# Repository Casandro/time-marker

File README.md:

# Time Marker

This is a small device designed to monitor the frequency of power grids.
It consists of a piece of hardware which generates GNSS synced audio markers, and isolates and down-scales it so both can be fed into a sound-card.

From there software will read the markers and generate down-sampled, but propperly timed audio files.

## Overall concept
```
          GNSS (GPS, Galileo, etc)
                   |
Mains grid---Time Marker hardware-----Line-IN of PC

```

## Hardware

The hardware will get an interrupt from the PPS signal from the GNSS receiver as well as the time via serial.
This will start playing a correlation sample, then some data containing the current time.
Optionally you can also put that signal onto an RS-232 port, which is useful for getting the PPS signal into your PC.

## Audio interface
The idea is that soundcards typically have very decent AD converters, usually having sample rates of at least 48kHz and sample depths of at least 16 Bits. It's hard to do that with easy to get chips.
However the clock of those is very much undefined, plus there is an unknown amount of latency between the analog input and the application getting the data.

To circumvent this, the hardware generates markers on one channel, so the other channel is free for whatever signal you want to sample.

### Format

The format is not yet defined, however it'll likely use either FSK or DTMF for the data.
There will be a sync mark at the beginning of the second, since this is when the timing error is lowest. It will be something with good correlation properties.

A DTMF tone typically is recommended to be at least 50 ms long with a pause of 20 ms between two digits. This means that in a second we could have 14 digits. Leaving some room for the second marker and silence at the end, we could, for exmample, have 10 digits per second. One marker, 8 data digits and one parity or stop digit. The advantage is that DTMF has discrete tones so we can easily have a gap at the end of the signal.

With FSK, we could, for example, have V.21 modulated bits. We'd probably have something like 256 data bits when we subtract run-in periods and the like. We probably need to re-sync it as part of the second mark.

## Software
No software is written so far, however it would probably work like this:

1. Determine the exact position of the second markers via cross correlation and sub sample interpolation. (The auto-correlation function will likely be triangular around it's center which we can use for sub sample accuracy)
2. Resample the second in the desired sample rate (e.g. 200 Hz)
3. Demodulate the data part of the signal to determine what second is read.
4. Store / process that second of data

Since we will likely not be able to get good data on harmonics, it may be sensible to only look at the 50 Hz peak. For this we can do an IQ demodulation at 50 Hz, downsample this to, for example, 10 or 25 Hz, and only store that IQ data. In principle we can also just store the phase data.

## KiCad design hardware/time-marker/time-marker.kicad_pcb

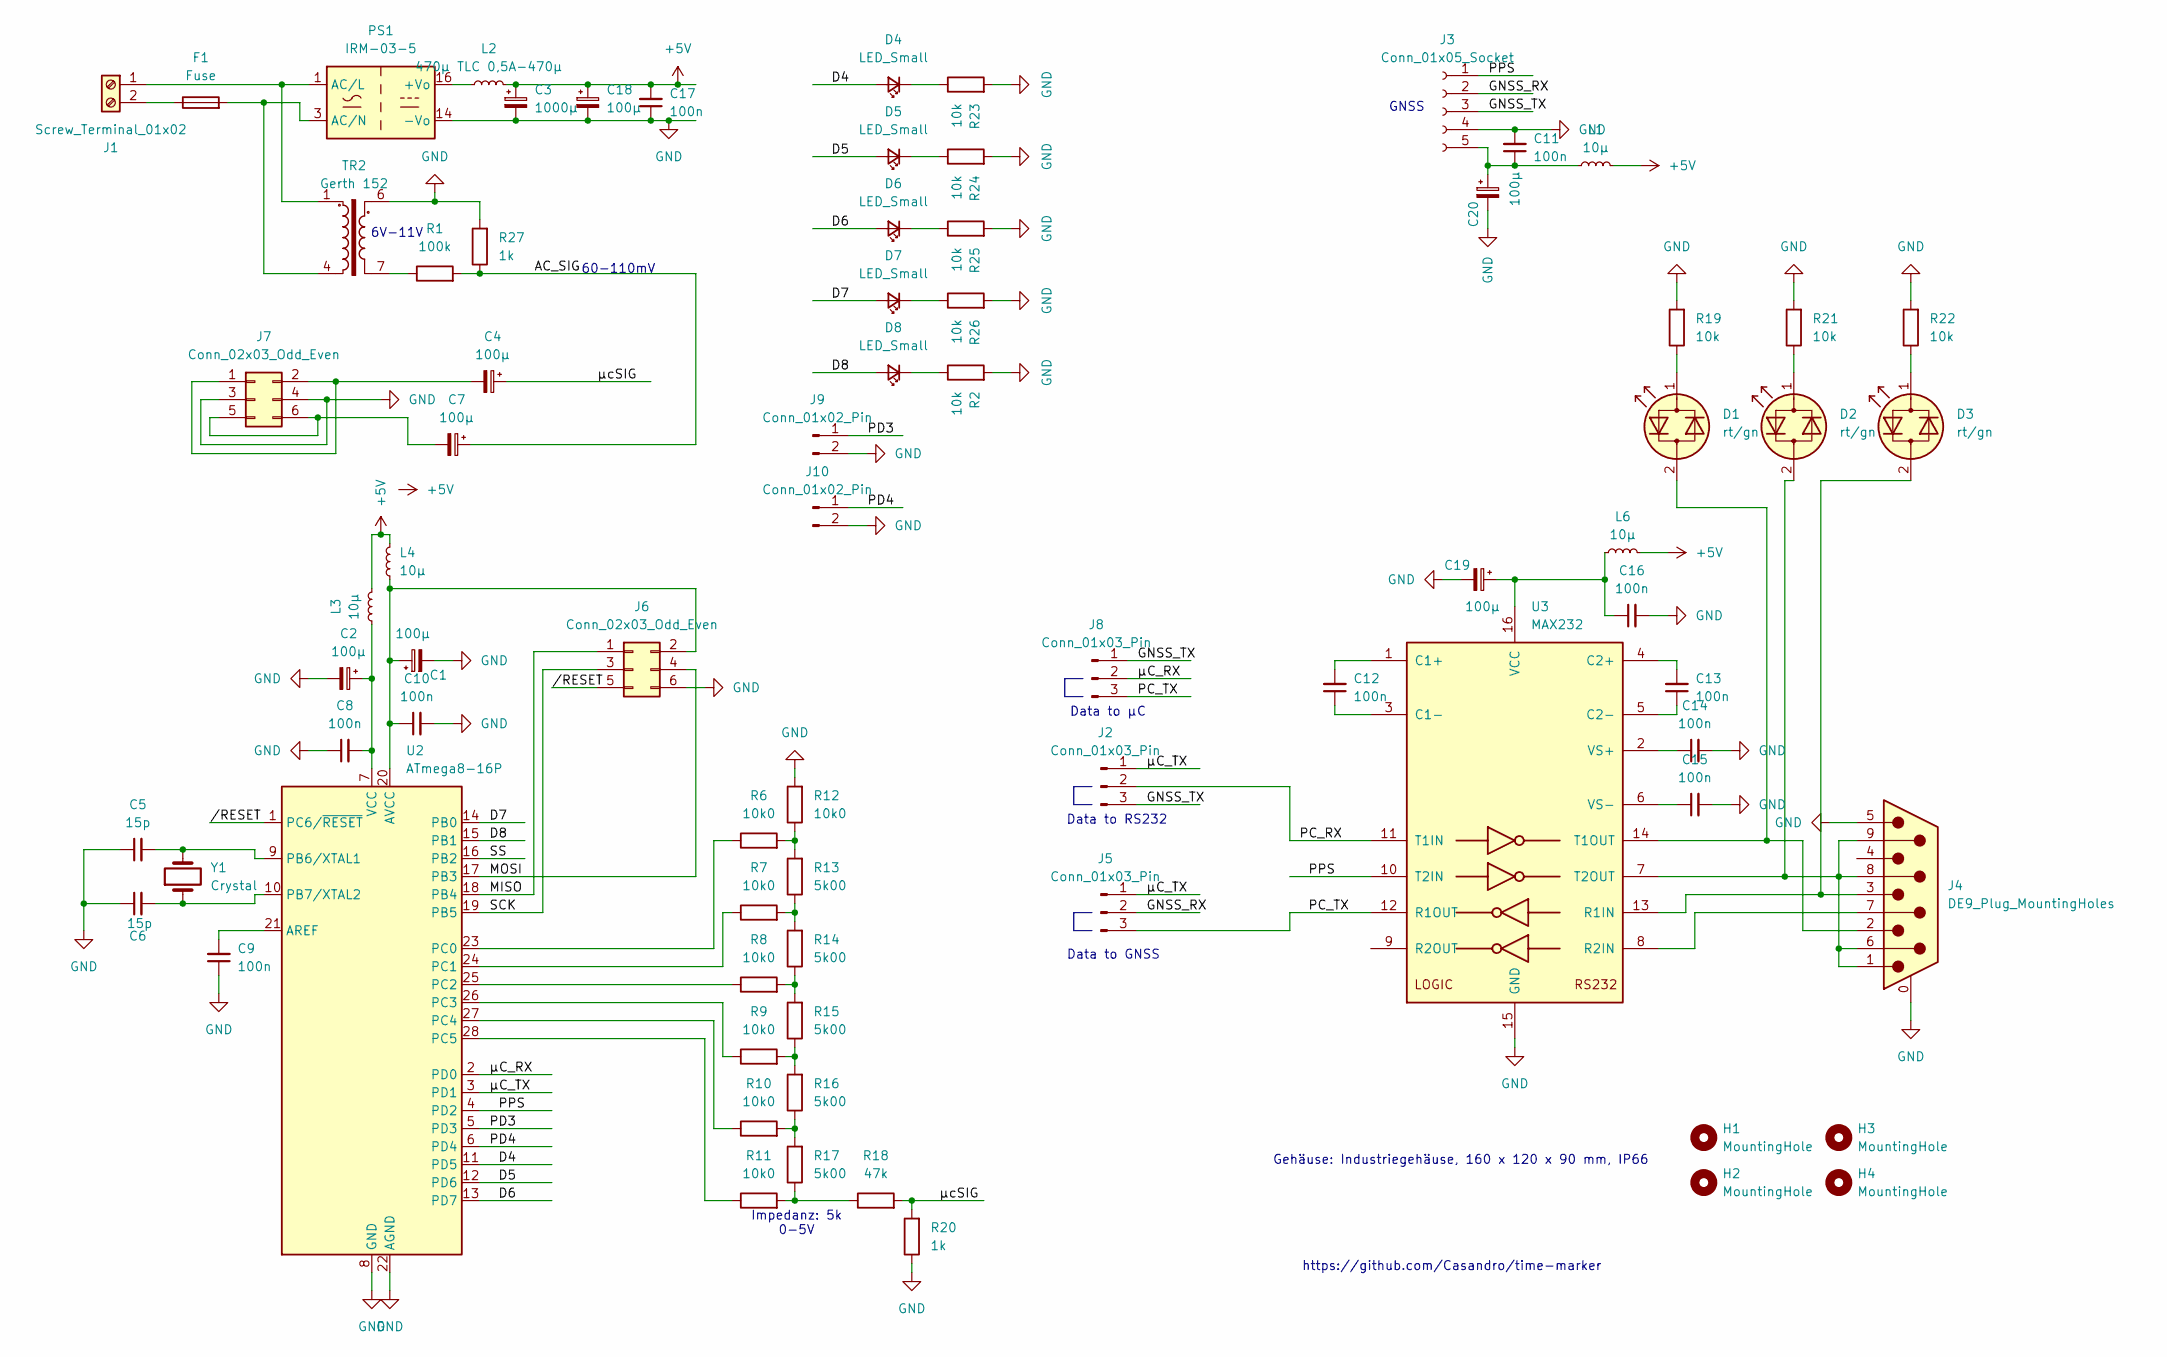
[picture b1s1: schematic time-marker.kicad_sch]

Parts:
C1, C2, C4, C7, C18, C19, C20: 100µ; CP_Radial_D5.0mm_P2.50mm
C3: 1000µ; CP_Radial_D10.0mm_P5.00mm
C5, C6: 15p; C_Disc_D3.0mm_W2.0mm_P2.50mm
C8, C9, C10, C11, C12, C13, C14, C15, C16, C17: 100n; C_Disc_D3.0mm_W2.0mm_P2.50mm
D1, D2, D3: rt/gn; LED_D3.0mm
D4, D5, D6, D7, D8: LED_Small; LED_D3.0mm_Clear
F1: Fuse; Fuse_Littelfuse_372_D8.50mm
H1, H2, H3, H4: MountingHole; MountingHole_4.3mm_M4
J1: Screw_Terminal_01x02; TerminalBlock_RND_205-00001_1x02_P5.00mm_Horizontal
J2, J5, J8: Conn_01x03_Pin; PinHeader_1x03_P2.54mm_Vertical
J3: Conn_01x05_Socket; PinSocket_1x05_P2.00mm_Horizontal
J4: DE9_Plug_MountingHoles; DSUB-9_Female_Horizontal_P2.77x2.84mm_EdgePinOffset4.94mm_H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
J6, J7: Conn_02x03_Odd_Even; IDC-Header_2x03_P2.54mm_Vertical
J9, J10: Conn_01x02_Pin; PinHeader_1x02_P2.54mm_Vertical
L1, L3, L4, L6: 10µ; L_Axial_L5.3mm_D2.2mm_P7.62mm_Horizontal_Vishay_IM-1
L2: 470µ TLC 0,5A-470µ; L_Toroid_Vertical_L16.3mm_W7.1mm_P7.11mm_Pulse_H
PS1: IRM-03-5; Converter_ACDC_MeanWell_IRM-03-xx_THT
R1: 100k; R_Axial_DIN0204_L3.6mm_D1.6mm_P7.62mm_Horizontal
R2, R19, R21, R22, R23, R24, R25, R26: 10k; R_Axial_DIN0204_L3.6mm_D1.6mm_P2.54mm_Vertical
R6, R7, R8, R9, R10, R11, R12: 10k0; R_Axial_DIN0204_L3.6mm_D1.6mm_P2.54mm_Vertical
R13, R14, R15, R16, R17: 5k00; R_Axial_DIN0204_L3.6mm_D1.6mm_P2.54mm_Vertical
R18: 47k; R_Axial_DIN0204_L3.6mm_D1.6mm_P7.62mm_Horizontal
R20, R27: 1k; R_Axial_DIN0204_L3.6mm_D1.6mm_P2.54mm_Vertical
TR2: Gerth 152; Transformer_Breve_TEZ-22x24
U2: ATmega8-16P; DIP-28_W7.62mm
U3: MAX232; DIP-16_W7.62mm
Y1: Crystal; Crystal_HC49-U_Vertical

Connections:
+5V: C3.1, C17.2, C18.1, L1.2, L2.2, L3.2, L4.2, L6.2
/AC_SIG: C7.1, R1.2, R27.1
/D4: D4.2 (A), U2.11 (PD5)
/D5: D5.2 (A), U2.12 (PD6)
/D6: D6.2 (A), U2.13 (PD7)
/D7: D7.2 (A), U2.14 (PB0)
/D8: D8.2 (A), U2.15 (PB1)
/GNSS_RX: J3.2, J5.2
/GNSS_TX: J2.3, J3.3, J8.1
/MISO: J6.1, U2.18 (PB4)
/MOSI: J6.4, U2.17 (PB3)
/PC_RX: J2.2, U3.11 (T1IN)
/PC_TX: J5.3, J8.3, U3.12 (R1OUT)
/PD3: J9.1, U2.5 (PD3)
/PD4: J10.1, U2.6 (PD4)
/PPS: J3.1, U2.4 (PD2), U3.10 (T2IN)
/SCK: J6.3, U2.19 (PB5)
/SS: U2.16 (PB2)
//RESET: J6.5, U2.1 (PC6/~RESET)
/µC_RX: J8.2, U2.2 (PD0)
/µC_TX: J2.1, J5.1, U2.3 (PD1)
/µcSIG: C4.1, R18.2, R20.2
GND: C1.2, C2.2, C3.2, C5.1, C6.1, C8.1, C9.1, C10.2, C11.2, C14.2, C15.2, C16.2, C17.1, C18.2, C19.2, C20.2, J3.4, J4.0 (PAD), J4.5, J6.6, J7.3, J7.4, J9.2, J10.2, PS1.14 (-Vo), R2.2, R12.2, R19.2, R20.1, R21.2, R22.2, R23.2, R24.2, R25.2, R26.2, R27.2, TR2.6, U2.8 (GND), U2.22 (AGND), U3.15 (GND)
unnamed: D1.2 (AK), J4.2, U3.14 (T1OUT)
unnamed: D1.1 (KA), R19.1
unnamed: D2.2 (AK), J4.1, J4.6, J4.8, J4.9, U3.7 (T2OUT)
unnamed: D2.1 (KA), R21.1
unnamed: D3.2 (AK), J4.3, U3.13 (R1IN)
unnamed: D3.1 (KA), R22.1
unnamed: D4.1 (K), R23.1
unnamed: D5.1 (K), R24.1
unnamed: D6.1 (K), R25.1
unnamed: D7.1 (K), R26.1
unnamed: D8.1 (K), R2.1
unnamed: J1.1, PS1.1 (AC/L), TR2.1
unnamed: F1.1, J1.2
unnamed: C11.1, C20.1, J3.5, L1.1
unnamed: C1.1, C10.1, J6.2, L4.1, U2.20 (AVCC)
unnamed: C4.2, J7.1, J7.2
unnamed: C7.2, J7.5, J7.6
unnamed: L2.1, PS1.16 (+Vo)
unnamed: F1.2, PS1.3 (AC/N), TR2.4
unnamed: R1.1, TR2.7
unnamed: R10.2, R16.1, R17.2
unnamed: R11.2, R17.1, R18.1
unnamed: R6.2, R12.1, R13.2
unnamed: R7.2, R13.1, R14.2
unnamed: R8.2, R14.1, R15.2
unnamed: R9.2, R15.1, R16.2
unnamed: C9.2, U2.21 (AREF)
unnamed: C5.2, U2.9 (PB6/XTAL1), Y1.2
unnamed: C6.2, U2.10 (PB7/XTAL2), Y1.1
unnamed: R6.1, U2.23 (PC0)
unnamed: R7.1, U2.24 (PC1)
unnamed: R8.1, U2.25 (PC2)
unnamed: R9.1, U2.26 (PC3)
unnamed: R10.1, U2.27 (PC4)
unnamed: R11.1, U2.28 (PC5)
unnamed: C2.1, C8.2, L3.1, U2.7 (VCC)
unnamed: C12.2, U3.1 (C1+)
unnamed: C12.1, U3.3 (C1-)
unnamed: C13.2, U3.4 (C2+)
unnamed: C13.1, U3.5 (C2-)
unnamed: J4.7, U3.8 (R2IN)
unnamed: C16.1, C19.1, L6.1, U3.16 (VCC)
unnamed: C14.1, U3.2 (VS+)
unnamed: C15.1, U3.6 (VS-)

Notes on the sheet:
Impedanz: 5k 0-5V
https://github.com/Casandro/time-marker
Gehäuse: Industriegehäuse, 160 x 120 x 90 mm, IP66
Data to µC
6V-11V
Data to GNSS
GNSS
60-110mV
Data to RS232

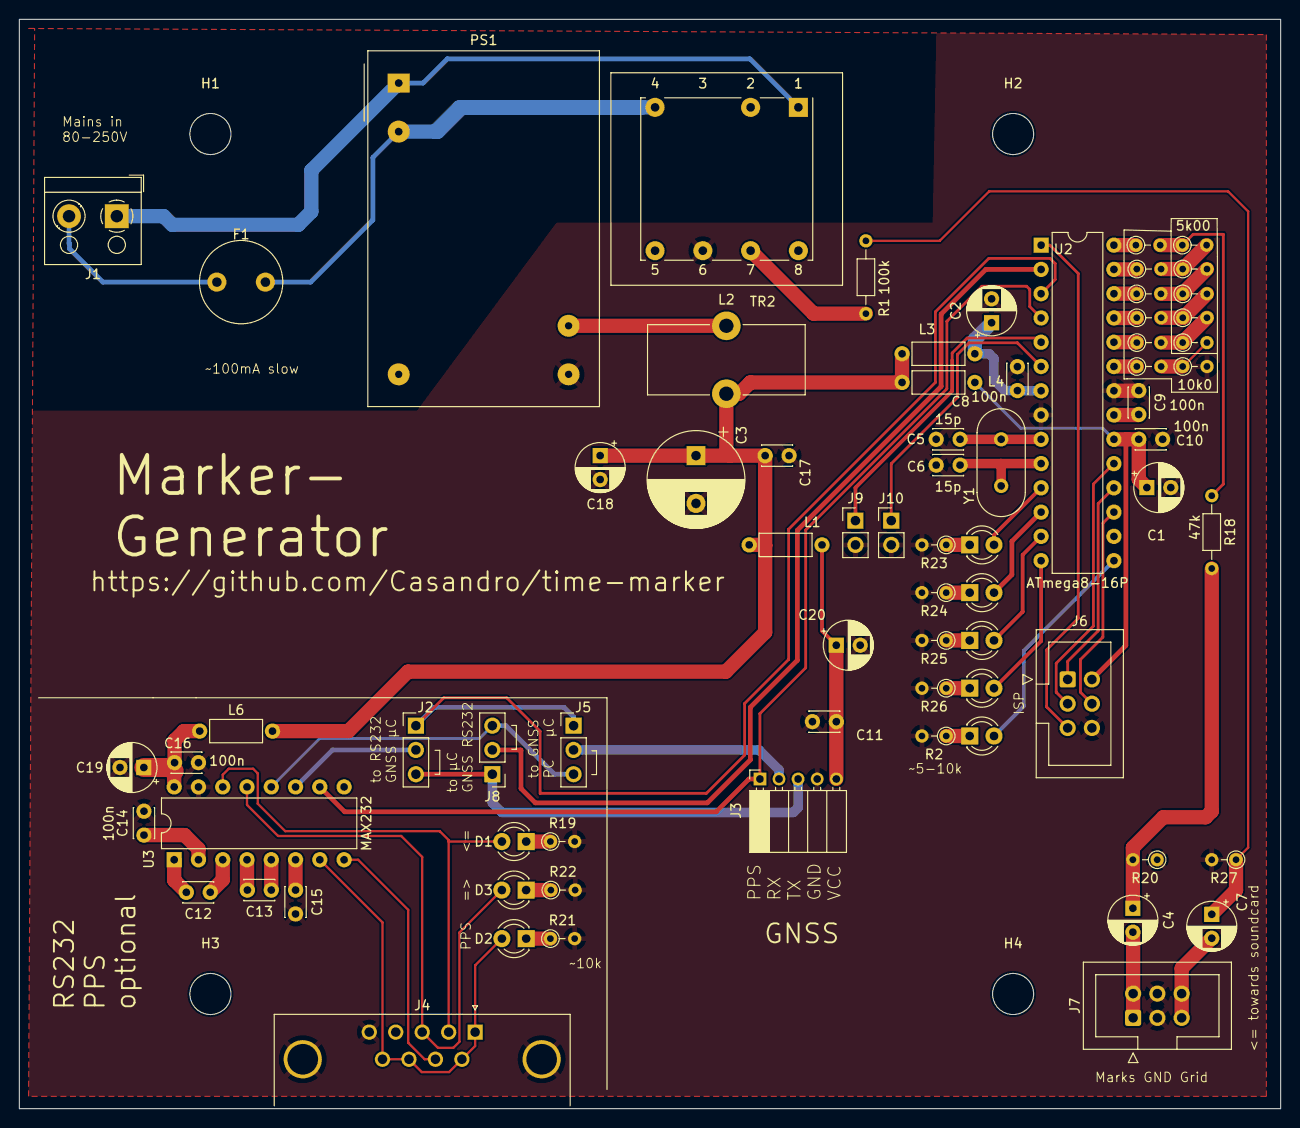
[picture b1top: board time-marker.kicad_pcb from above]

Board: 2 copper layers, 132.0 x 114.0 mm, 77 parts (0 on the bottom side), 66 nets.

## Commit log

2025-08-09 Added images and readme
2025-08-09 More info on the potential marker signal
